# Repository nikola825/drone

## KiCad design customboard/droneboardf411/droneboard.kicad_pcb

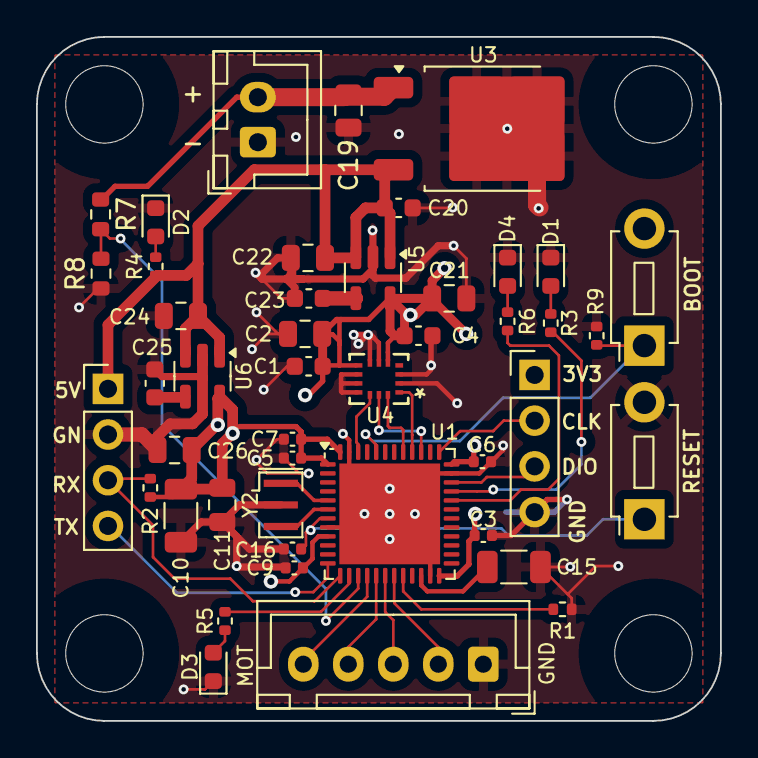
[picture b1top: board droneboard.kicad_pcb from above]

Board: 4 copper layers, 38.0 x 38.0 mm, 49 parts (0 on the bottom side), 33 nets.

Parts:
C1, C20: 100n; C_0603_1608Metric
C2: 2.2u; C_0805_2012Metric
C3, C5, C6, C7, C9, C16: 100n; C_0402_1005Metric
C4, C23, C25: 10n; C_0603_1608Metric
C10: 10u; C_1206_3216Metric
C11, C21, C22, C24, C26: 1u; C_0805_2012Metric
C15: 4.7u; C_1206_3216Metric
C19: 330n; C_0805_2012Metric
D1: YELLOW_LED; LED_0603_1608Metric
D2: RED_LED; LED_0603_1608Metric
D3: GREEN_LED; LED_0603_1608Metric
D4: BLUE_LED; LED_0603_1608Metric
H2, H4, H5, H6: MountingHole_Pad; MountingHole_4.3mm_M4_DIN965
J1: Conn_01x04; PinHeader_1x04_P2.54mm_Vertical
J3: Conn_01x05_Pin; JST_XH_B5B-XH-A_1x05_P2.50mm_Vertical
J4: Conn_01x02_Pin; JST_XH_B2B-XH-A_1x02_P2.50mm_Vertical
J7: Conn_01x04_Odd_Even; PinHeader_1x04_P2.54mm_Vertical
R1, R2, R9: 10K; R_0402_1005Metric
R3, R4, R5, R6: 1K; R_0402_1005Metric
R7: 10K; R_0603_1608Metric
R8: 1K; R_0603_1608Metric
SW1, SW2: SW_Push; SW_PUSH_1P1T_6x3.5mm_H4.3_APEM_MJTP1243
U1: STM32F411CEUx; QFN-48-1EP_7x7mm_P0.5mm_EP5.6x5.6mm
U3: L78M05CDT; TO-252-2
U4: ICM-42688-P; LGA14_2P5X3X0P91_IVS-L
U5, U6: LDK130M33R; SOT-23-5
Y2: CSTNE20M0V53Z000R0; Resonator_SMD_Murata_CSTxExxV-3Pin_3.0x1.1mm

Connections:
/5V: C20.2, C22.1, C24.1, J1.1, R4.1, U3.3 (OUT), U5.1 (IN), U5.3 (EN), U6.1 (IN), U6.3 (EN)
/12V: C19.2, J4.2, R7.1, U3.1 (IN)
/BLUE: R6.1, U1.32 (PA11)
/BOOT: R9.2, SW2.1, U1.44 (BOOT0)
/GND: C1.1, C2.2, C3.2, C4.1, C5.2, C6.2, C7.2, C9.2, C10.1, C11.1, C15.2, C16.2, C19.1, C20.1, C21.2, C22.2, C23.1, C24.2, C25.1, C26.2, D1.1 (K), D2.1 (K), D3.1 (K), D4.1 (K), J1.2, J3.1, J4.1, J7.4, R1.2, R8.1, R9.1, SW1.2, U1.8 (VSSA), U1.23 (VSS), U1.35 (VSS), U1.47 (VSS), U1.49 (VSS), U3.2 (GND), U4.2 (RESV), U4.3 (RESV), U4.6 (GND), U4.7 (RESV), U4.9 (INT2/FSYNC/CLKIN), U4.10 (RESV), U4.11 (RESV), U5.2 (GND), U6.2 (GND), Y2.2
/GREEN: R5.1, U1.14 (PA4)
/IMU_CS: U1.46 (PB9), U4.12 (AP_CS)
/MISO: U1.40 (PB4), U4.1 (AP_SDO/AP_AD0)
/MOSI: U1.41 (PB5), U4.14 (AP_SDA/AP_SDIO/AP_SDI)
/MOTOR0: J3.2, U1.19 (PB1)
/MOTOR1: J3.3, U1.18 (PB0)
/MOTOR2: J3.4, U1.17 (PA7)
/MOTOR3: J3.5, U1.16 (PA6)
/RESET1: C16.1, SW1.1, U1.7 (NRST)
/RX3: J1.3, R2.1, U1.13 (PA3)
/SCK: U1.39 (PB3), U4.13 (AP_SCL/AP_SCLK)
/SWCLK: J7.2, U1.37 (PA14)
/SWDIO: J7.3, U1.34 (PA13)
/TX3: J1.4, U1.12 (PA2)
/VBATMON: R7.2, R8.2, U1.15 (PA5)
/VGYRO: C1.2, C2.1, C4.2, C21.1, U4.5 (VDDIO), U4.8 (VDD), U5.5 (OUT)
/VMCU: C3.1, C5.1, C6.1, C7.1, C9.1, C10.2, C11.2, C26.1, J7.1, R2.2, SW2.2, U1.1 (VBAT), U1.9 (VDDA), U1.24 (VDD), U1.36 (VDD), U1.48 (VDD), U6.5 (OUT)
/YELLOW: R3.1, U1.33 (PA12)
unnamed: D1.2 (A), R3.2
unnamed: D2.2 (A), R4.2
unnamed: D3.2 (A), R5.2
unnamed: D4.2 (A), R6.2
unnamed: R1.1, U1.20 (PB2)
unnamed: U1.5 (PH0), Y2.1
unnamed: U1.6 (PH1), Y2.3
unnamed: C15.1, U1.22 (VCAP1)
unnamed: C23.2, U5.4 (BP)
unnamed: C25.2, U6.4 (BP)

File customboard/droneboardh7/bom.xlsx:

|  |  | xxxx xxxx xxxxx xxPCS BOM (Sample Bill of Materials)
Item # | *Designator | *Qty | Manufacturer | *Mfg Part # | Description / Value | *Package/Footprint | Type | Your Instructions / Notes
1 | C4, C23, C25 | 3 | Don’t care | Don’t care | CAP CER 10nF 16V X7R 0603 | 0603 | SMD | Don’t care about model/manufacturer, just make sure it fits description
2 | C1, C20 | 2 | Don’t care | Don’t care | CAP CER 100nF 16V X7R 0603 | 0603 | SMD | Don’t care about model/manufacturer, just make sure it fits description
3 | C3, C5, C6, C7, C9, C16 | 6 | Don’t care | Don’t care | CAP CER 100nF 16V X7R 0402 | 0402 | SMD | Don’t care about model/manufacturer, just make sure it fits description
4 | C19 | 1 | Don’t care | Don’t care | CAP CER 330nF 25V X7R 0805 | 0805 | SMD | Don’t care about model/manufacturer, just make sure it fits description
5 | C11, C21, C22, C24, C26 | 5 | Don’t care | Don’t care | CAP CER 1uF 16V X5R 0805 | 0805 | SMD | Don’t care about model/manufacturer, just make sure it fits description
6 | C2 | 1 | Don’t care | Don’t care | CAP CER 2.2uF 16V X7R 0805 | 0805 | SMD | Don’t care about model/manufacturer, just make sure it fits description
 | C15 | 1 | Don’t care | Don’t care | CAP CER 4.7uF 16V X7R 1206 | 1206 | SMD | Don’t care about model/manufacturer, just make sure it fits description
 | C10 | 1 | Don’t care | Don’t care | CAP CER 10uF 16V X7R 1206 | 1206 | SMD | Don’t care about model/manufacturer, just make sure it fits description
 | D1 | 1 | Don’t care | Don’t care | LED SMD Yellow 2V 20ma 0603 | 0603 | SMD | Don’t care about model/manufacturer, just make sure it fits description
 | D2 | 1 | Don’t care | Don’t care | LED SMD Red 2V 20ma 0603 | 0603 | SMD | Don’t care about model/manufacturer, just make sure it fits description
 | D3 | 1 | Don’t care | Don’t care | LED SMD Green 2V 20ma 0603 | 0603 | SMD | Don’t care about model/manufacturer, just make sure it fits description
 | D4 | 1 | Don’t care | Don’t care | LED SMD Blue 2V 20ma 0603 | 0603 | SMD | Don’t care about model/manufacturer, just make sure it fits description
 | R1,R2,R9 | 3 | Don’t care | Don’t care | RES 10K OHM 0.1W 1% 0402 SMD | 0402 | SMD | Don’t care about model/manufacturer, just make sure it fits description
 | R7 | 1 | Don’t care | Don’t care | RES 10K OHM 0.1W 1% 0603 SMD | 0603 | SMD | Don’t care about model/manufacturer, just make sure it fits description
 | R3, R4, R5, R6 | 4 | Don’t care | Don’t care | RES 1K OHM 0.1W 1% 0402 SMD | 0402 | SMD | Don’t care about model/manufacturer, just make sure it fits description
 | R8 | 1 | Don’t care | Don’t care | RES 1K OHM 0.1W 1% 0603 SMD | 0603 | SMD | Don’t care about model/manufacturer, just make sure it fits description
 | U1 | 1 | STMicroelectronics | STM32F411CEU6 | ARM Microcontrollers - MCU High-performance access line, Arm Cortex-M4 core DSP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 | QFN-48 | SMD
 | U3 | 1 | STMicroelectronics | L78M05CDT | Linear Voltage Regulators 5.0V 0.5A Positive | TO-252-2 | SMD
 | U4 | 1 | TDK Invensense | ICM-42688-P | IMUs - Inertial Measurement Units 6 Axis IMU Motion Tracking | LGA-14 3x2.5 P0.5 | SMD
 | U5,U6 | 2 | STMicroelectronics | LDK130M33R | LDO Voltage Regulators 300mA low Q LDO 1.9 to 5.5V 100mV | SOT-23-5 | SMD
 | Y2 | 1 | Murata Electronics | CSTNE20M0V53Z000R0 | Resonators 20.0 MHZ 15PF | 3-SMD, Non-Standard | SMD
Need a quick and accurante quote? Need an efficient production? Please read SMT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
Click for Instructions on How to Create a BOM
